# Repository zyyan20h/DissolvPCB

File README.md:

# DissolvPCB 
### Fully Recyclable Electronics with Liquid Metal Conductors and 3D-Printed PVA Substrates
DissolvPCB is a fully recyclable printed circuit board assembly (PCBA) manufacturing technique 
that utilizes affordable FDM 3D printing with Polyvinyl Alcohol (PVA) as a water-soluble substrate 
and eutectic gallium-indium (EGaIn) as the conductive material. 

This Github repository contains the Python macro component used during the DissolvPCB fabrication process. 
The macro enables users to design custom PCB assemblies using standard practices, then automatically
convert the design into a 3D model ready to be printed. Also included are some PCB design examples that 
were used for the demonstration of the DissolvPCB fabrication process. 
Listed below are the prerequisites and instructions on how to utilize this tool. 
Detailed instructions on the entire DisssolvPCB fabrication process can be found under [DissolvPCB Processs Details](DissolvPCB_Process_Details.md).

Please see the [paper](https://www.arxiv.org/abs/2507.22193) for more details on development, implementation, and evaluation of DissolvPCB, and if you use DissolvPCB in your work, please consider to cite the following paper:
```
@article{yan2025dissolvpcb,
  title={DissolvPCB: Fully Recyclable 3D-Printed Electronics with Liquid Metal Conductors and PVA Substrates},
  author={Yan, Zeyu and Hong, SuHwan and Hester, Josiah and Cheng, Tingyu and Peng, Huaishu},
  publisher = {Association for Computing Machinery},
  url = {https://doi.org/10.1145/3746059.3747604},
  year={2025}，
  booktitle = {Proceedings of the 38th Annual ACM Symposium on User Interface Software and Technology}
}
```

## Installation 

### Prerequisites
  - Python 3.0.0 or above
  - FreeCAD 1.0.0 or above
    - https://www.freecad.org/downloads.php
  - KiCAD 8.0.7 or above
    - https://www.kicad.org/download/

### KiCAD Libraries Installation
  - Add Symbol Library
    - Located in /libray/PVA_board.kicad_sym
    - Add by going to: Symbol Editor -> File -> Add Library
  - Add Footprint Library
    - Located in /library/PVA_board.pretty
    - Add by going to: Footprint Editor -> File -> Add Library
  - Copy 3D moddels to KiCAD 3D Models
    - Copy the folder /library/PVA_Board_3Dmodels into directory
    - Set Global Variable "KICAD_3DMODEL_DIR" to correct directory
      - Usually Located under C:\Program Files\KiCad\8.0\share\kicad\3dmodels
      - You can locate the direcotry by going to the KiCAD project window, then Preferences -> Configure Paths
   
## DissolvPCB Design in KiCAD
### PCB Schematic Design
  If you have imported the libraries as described above, the schematic design follows standard procedues.
  During the footprint assignment at the end of your schematic design procecss, verify that 
  footprints are from the PVA_Board library.
    
### PCB Layout Design
  To ensure compatibility with the DissolvPCB fabrication process, a few settings must be changed first. 
  The DRC settings can simply be imported from /KiCAD/DRC_Import_Prj/DRC_Import/DRC_Import.kicad_pcb, using the "Import Settings from Another Board" button under File -> Board Setup. 
  By importing "Design rule constraints", "Predefined track & via dimensions", and "Violation severities" (optional), 
  the PCB design will become compatible with the DissolvPCB fabrication process. (See attached below)

## Macro Execution
FreeCAD has built-in support for Python macros. 
To run, open the Python script by going to File -> Open and open /Python/create.py.
Then, run the macro by going to Macro -> Run Macro. 
Note that the boolean process step at the end can take some time depending on the complexity of your design and your compute power. 
Therefore, it is recommended that you run the macro on a system with a more powerful CPU if possible.

### Macro Functions
The Python scripts contain code comments throughout to help users debug and modify. Overall, the 4 main steps of the macro includes:
- Trace & Pad Generation
- DissolvPCB Body Creation
- 3D Footprint Insertion
- Boolean Operation

Except for the Boolean Operation, these parts are independant of each other. 
Thus, it is possible to run any combination of of the first 3 as desired. 

*Note: If the boolean operation fails from an error relating to 'multiple bodies', you may have to enable a setting. 
Go to Edit -> Preferences -> Part/Part Design -> Experimental -> check "Allow multiple solids in Part Design Body by Defualt"

## Examples 

Some KiCAD Designs are provided, which are listed below.
Note that Circuit_sample_01, circuit_sample_02, and ESP_Speaker designs are directly compatible with the macro, and does not require any modifications to replicate our designs. 
  - /KiCAD/circuit_sample/circuit_sample_01
    - Hall Sensor & ATTiny85 design, used throughout the paper
      
  - /KiCAD/circuit_sample/circuit_sample_02
    - Identical Hall Sensor & ATTiny85 design, but with different board outline
	- /KiCAD/circuit_sample/recycled_driver
		- Motor driver circuit design, used to demonstrate the capabilities of the recycled PVA filament
  - /KiCAD/ESP_Breakout
    - Breakout board(s) designed to house the ESP32 board used for the ESP_Speaker Design
    - The version utilized on the paper is the "2mm_2row_esp_breakout" design
  - /KiCAD/ESP_Speaker
    - ESP32-based bluetooth speaker design.
    - The exact design used on the paper demo is "rev_2_ESP_Speaker_2row_esp"
    - Alternatively, a design with components only on one side is under "rev_3_ESP_Speaker_2row_esp"
      
  - /KiCAD/fidget
    - Fidget toy example used on the paper, utilizing a 3D circuit design process.

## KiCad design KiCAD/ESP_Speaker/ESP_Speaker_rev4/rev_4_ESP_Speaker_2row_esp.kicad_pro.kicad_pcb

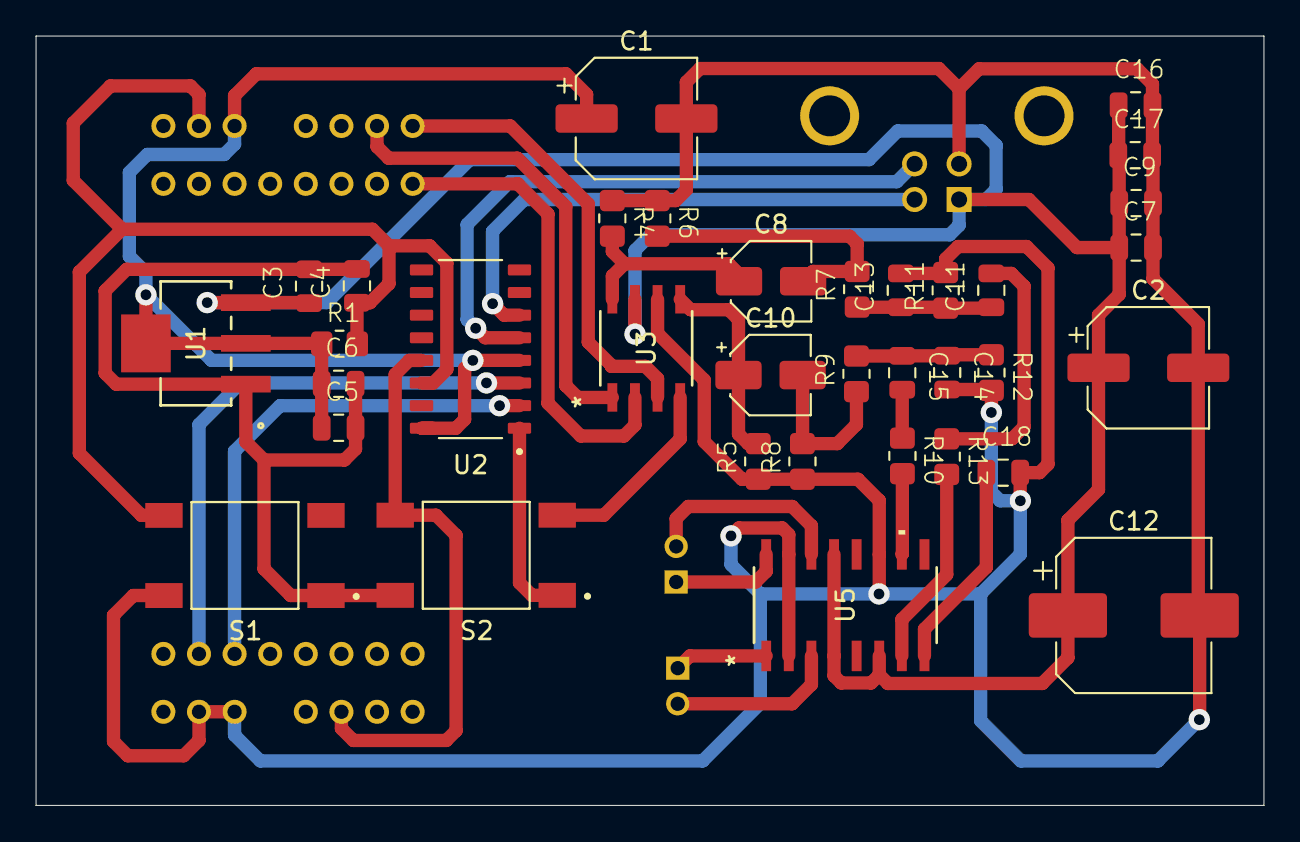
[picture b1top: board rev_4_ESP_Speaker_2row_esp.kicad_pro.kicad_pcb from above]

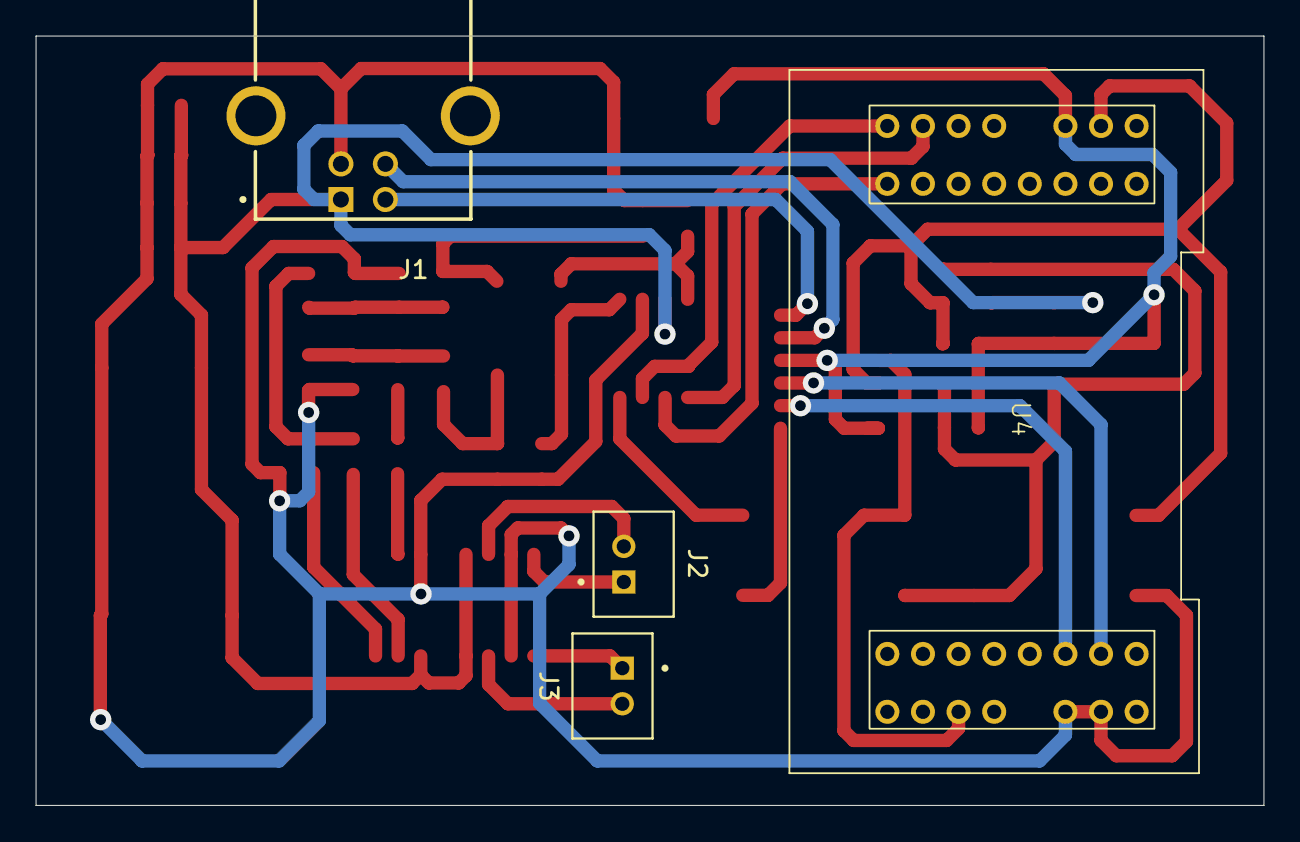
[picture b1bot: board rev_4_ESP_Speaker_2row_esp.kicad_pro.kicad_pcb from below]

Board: 2 copper layers, 69.0 x 43.2 mm, 39 parts (4 on the bottom side), 28 nets.

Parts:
C1, C2: 22uF; CP_Elec_6.3x5.4
C3, C5: 100nF; C-0805
C4, C7, C16, C17: 1uF; C-0805
C6, C9: 0.1uF; C-0805
C8, C10: 3.3uF; CP_Elec_4x5.4
C11, C15: 0.47uF; C-0805
C12: 470uF; CP_Elec_8x10.5
C13, C14: 6nF; C-0805
C18: .1uF; C-0805
J1: USB-B; SAMTEC_USB-B-S-X-X-TH
J2: Audio_R; JST_B2B-PH
J3: Audio_L; JST_B2B-PH
R1, R6, R8: 10k; R-0805
R4, R5: 267k; R-0805
R7, R9: 560; R-0805
R10, R13: 20k; R-0805
R11, R12: 22k; R-0805
S1, S2: 1571527-2; SW_4pin_SMD
U1: AMS1117; SOT_AMS_ADS-M
U2: CH340C; CH430C_SOP16
U3: CS4334-KSZ; CIR-SOIC-8_W150-M
U4: 2mm_2row_esp32_breakout
U5: PAM8403DR; SOIC_8403DR_PAM8403-M

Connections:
+3.3V: C1.1, C5.1, C6.1, R1.1, U1.2 (VOUT), U1.4 (EPAD), U2.4 (V3), U2.16 (VCC), U4.1 (3V3)
+5V: C2.1, C3.1, C7.1, C9.1, C12.1, C16.1, C17.1, J1.1 (VCC), U1.3 (VIN), U3.7 (VA), U5.4 (PVDD), U5.6 (VDD), U5.13 (PVDD)
/Audio-Amp/Audio_R: C14.1, C15.1, R9.2, R12.1
/Audio-Amp/Audo_L: C11.1, C13.1, R7.1, R11.1
/Audio-Amp/L+: J3.1, U5.1 (+OUT_L)
/Audio-Amp/L-: J3.2, U5.3 (-OUT_L)
/Audio-Amp/R+: J2.1, U5.16 (+OUT_R)
/Audio-Amp/R-: J2.2, U5.14 (-OUT_R)
/BCLK: U3.2 (DEM/SCLK), U4.11 (IO27)
/Data: U3.1 (SDATA), U4.13 (IO12)
/EN: C4.1, R1.2, S1.3, S1.4, U2.14 (~RTS), U4.2 (EN)
/IO0: S2.3, S2.4, U2.13 (~DTR), U3.4 (MCLK), U4.29 (IO0)
/RX_ESP: U2.2 (TXD), U4.21 (RXD0)
/TX_ESP: U2.3 (RXD), U4.20 (TXD0)
/WS: U3.3 (LRCK), U4.12 (IO14)
D+: J1.3 (D+), U2.5 (UD+)
D-: J1.2 (D-), U2.6 (UD-)
GND: C1.2, C2.2, C3.2, C4.2, C5.2, C6.2, C7.2, C9.2, C12.2, C13.2, C14.2, C16.2, C17.2, C18.2, J1.4 (GND), R4.1, R5.1, R6.1, R8.1, R11.2, R12.2, S1.1, S1.2, S2.1, S2.2, U1.1 (GND/ADJ), U2.1 (GND), U3.6 (AGND), U4.16 (GND), U4.17 (GND), U5.2 (PGND), U5.11 (GND), U5.15 (PGND)
unnamed: C8.2, R6.2, R7.2
unnamed: C10.2, R8.2, R9.1
unnamed: C11.2, R13.1
unnamed: C15.2, R10.1
unnamed: J1.S1 (SHIELD), J1.S2 (SHIELD)
unnamed: C8.1, R4.2, U3.8 (AOUTL)
unnamed: C10.1, R5.2, U3.5 (AOUTR)
unnamed: R13.2, U5.7 (INL)
unnamed: R10.2, U5.10 (INR)
unnamed: C18.1, U5.8 (VREF)

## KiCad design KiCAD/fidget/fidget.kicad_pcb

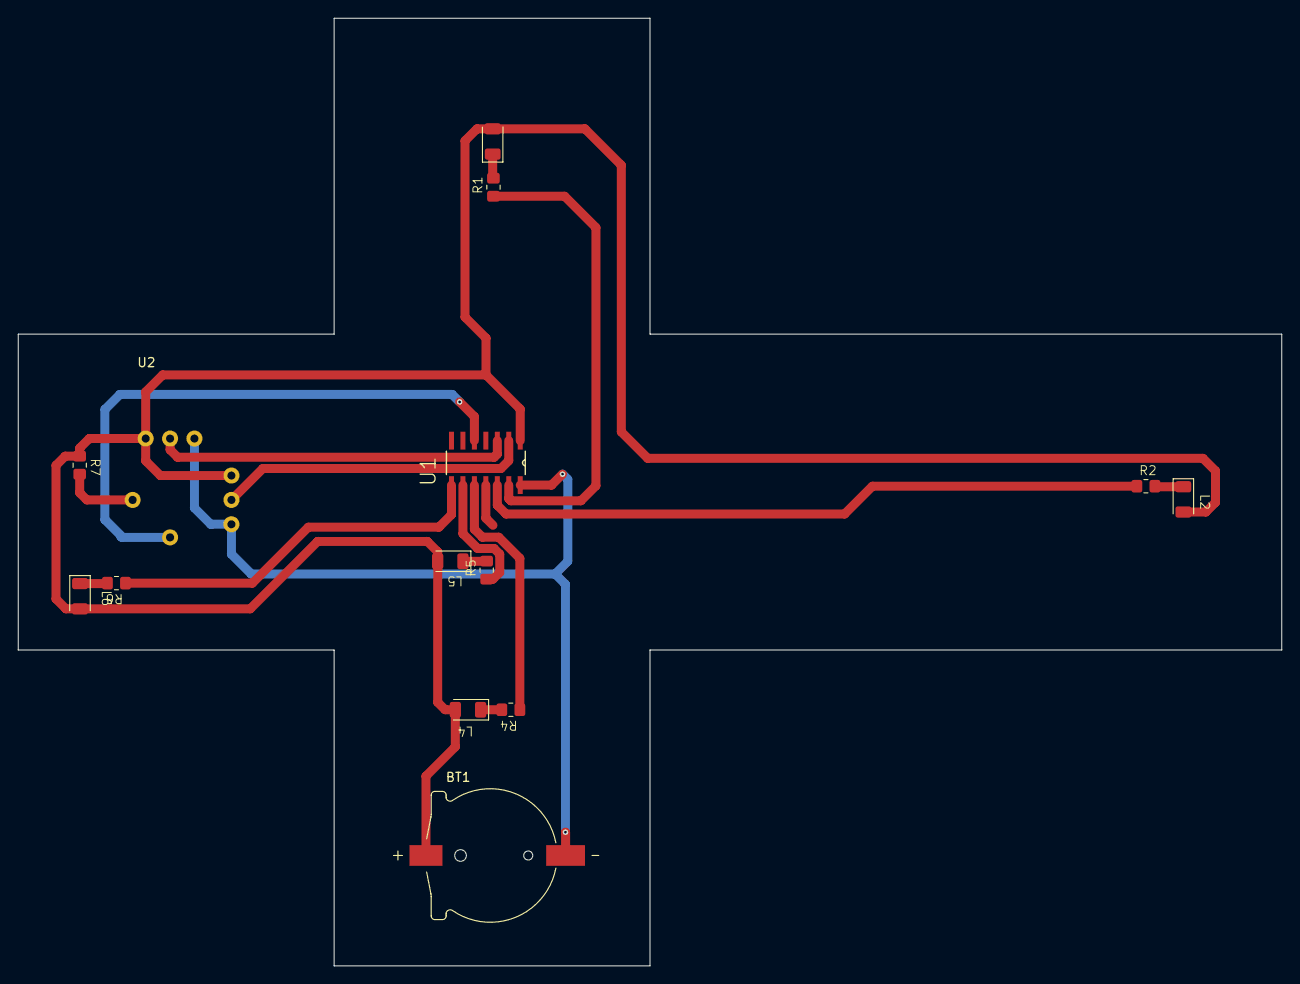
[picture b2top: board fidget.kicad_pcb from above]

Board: 2 copper layers, 140.0 x 105.0 mm, 14 parts (0 on the bottom side), 16 nets.

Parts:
BT1: CH291-1220LF; BAT_CH291-1220LF
L1, L2, L4, L5, L6: LED-1206
R1, R2, R4, R5, R6, R7: R-0805
U1: SOIC-14
U2: COM-09032; Joystick

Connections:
/GND: BT1.N, U1.14, U2.H3 (H-), U2.V3 (V-)
/L1: R1.1, U1.13
/L2: R2.1, U1.12
/L4: R4.1, U1.10
/L5: R5.1, U1.9
/L6: R6.1, U1.8
/S1: U1.3, U2.V2 (V)
/S2: U1.2, U2.H2 (H)
/S3: U1.5, U2.Sb
/VCC: BT1.P, L1.2 (A), L2.2 (A), L4.2 (A), L5.2 (A), L6.2 (A), R7.1, U1.1, U2.H1 (H+), U2.V1 (V+)
unnamed: L1.1 (K), R1.2
unnamed: L2.1 (K), R2.2
unnamed: L4.1 (K), R4.2
unnamed: L5.1 (K), R5.2
unnamed: L6.1 (K), R6.2
unnamed: R7.2, U2.Sa

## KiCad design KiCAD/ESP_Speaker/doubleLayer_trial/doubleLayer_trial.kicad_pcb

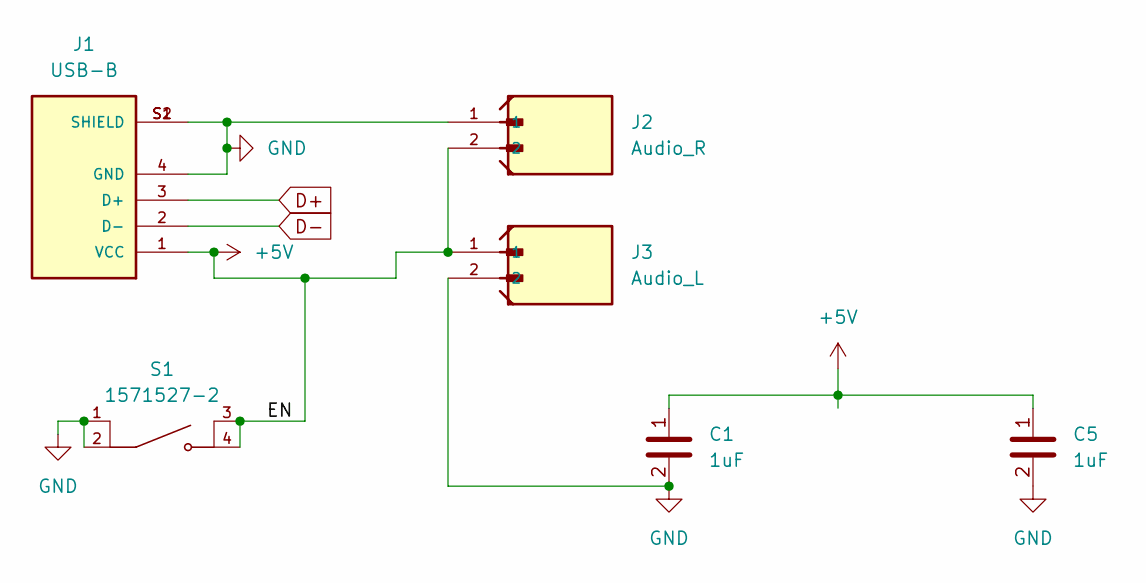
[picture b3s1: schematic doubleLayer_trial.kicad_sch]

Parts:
C1, C5: 1uF; C-0805
J1: USB-B; SAMTEC_USB-B-S-X-X-TH
J2: Audio_R; JST_B2B-PH
J3: Audio_L; JST_B2B-PH
S1: 1571527-2; SW_4pin_SMD

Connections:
+5V: C1.1, C5.1, J1.1 (VCC), J2.2, J3.1, S1.3, S1.4
D+: J1.3 (D+)
D-: J1.2 (D-)
GND: C1.2, C5.2, J1.4 (GND), J1.S1 (SHIELD), J1.S2 (SHIELD), J2.1, J3.2, S1.1, S1.2

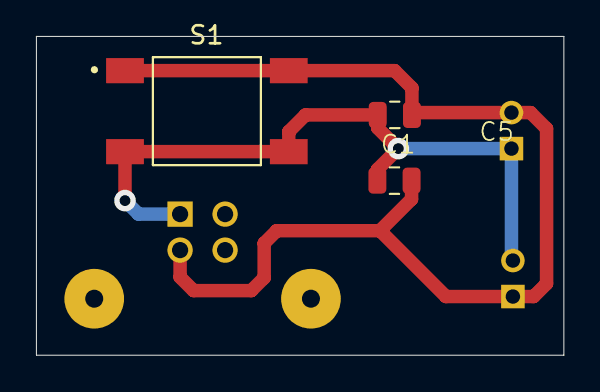
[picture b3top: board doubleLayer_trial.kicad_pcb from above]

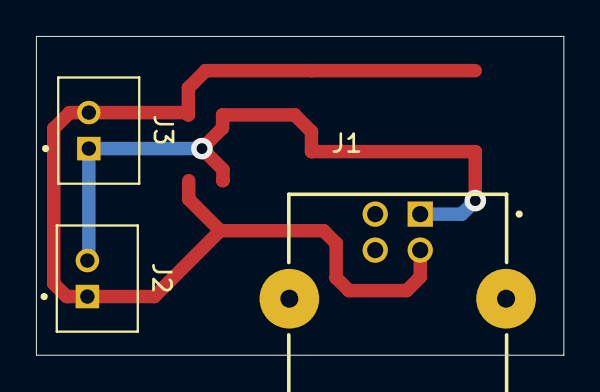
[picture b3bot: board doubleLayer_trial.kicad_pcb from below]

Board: 2 copper layers, 29.3 x 17.7 mm, 6 parts (3 on the bottom side), 2 nets.

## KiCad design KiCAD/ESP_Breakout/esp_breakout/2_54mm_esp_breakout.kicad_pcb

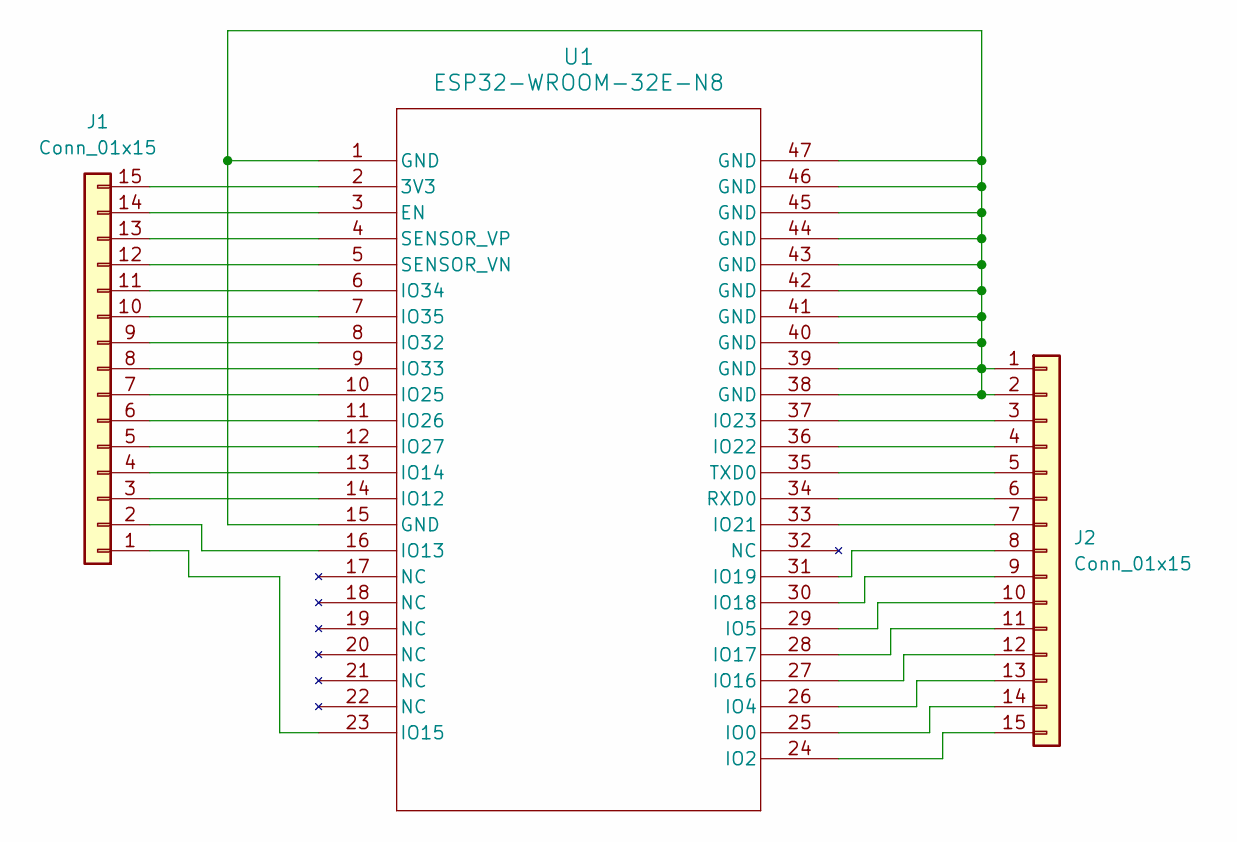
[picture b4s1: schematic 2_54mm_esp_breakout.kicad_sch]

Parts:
J1, J2: Conn_01x15; PinHeader_1x15_P2.54mm_Vertical
U1: ESP32-WROOM-32E-N8; ESP32­WROOM­32E_EXP

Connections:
unnamed: J1.1, U1.23 (IO15)
unnamed: J1.2, U1.16 (IO13)
unnamed: J1.3, U1.14 (IO12)
unnamed: J1.4, U1.13 (IO14)
unnamed: J1.5, U1.12 (IO27)
unnamed: J1.6, U1.11 (IO26)
unnamed: J1.7, U1.10 (IO25)
unnamed: J1.8, U1.9 (IO33)
unnamed: J1.9, U1.8 (IO32)
unnamed: J1.10, U1.7 (IO35)
unnamed: J1.11, U1.6 (IO34)
unnamed: J1.12, U1.5 (SENSOR_VN)
unnamed: J1.13, U1.4 (SENSOR_VP)
unnamed: J1.14, U1.3 (EN)
unnamed: J1.15, U1.2 (3V3)
unnamed: J2.1, J2.2, U1.1 (GND), U1.15 (GND), U1.38 (GND), U1.39 (GND), U1.40 (GND), U1.41 (GND), U1.42 (GND), U1.43 (GND), U1.44 (GND), U1.45 (GND), U1.46 (GND), U1.47 (GND)
unnamed: J2.3, U1.37 (IO23)
unnamed: J2.4, U1.36 (IO22)
unnamed: J2.5, U1.35 (TXD0)
unnamed: J2.6, U1.34 (RXD0)
unnamed: J2.7, U1.33 (IO21)
unnamed: J2.8, U1.31 (IO19)
unnamed: J2.9, U1.30 (IO18)
unnamed: J2.10, U1.29 (IO5)
unnamed: J2.11, U1.28 (IO17)
unnamed: J2.12, U1.27 (IO16)
unnamed: J2.13, U1.26 (IO4)
unnamed: J2.14, U1.25 (IO0)
unnamed: J2.15, U1.24 (IO2)

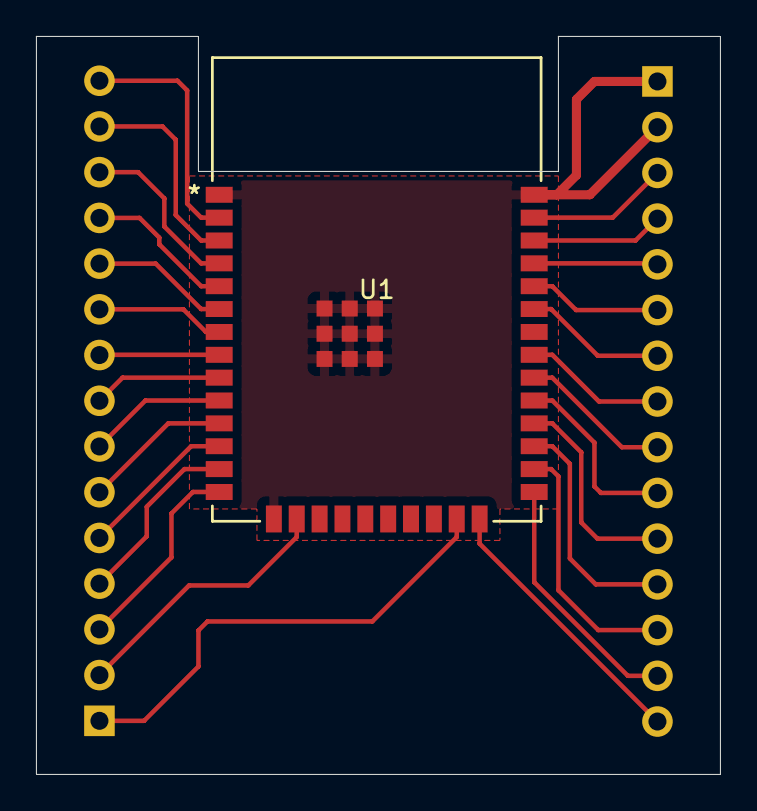
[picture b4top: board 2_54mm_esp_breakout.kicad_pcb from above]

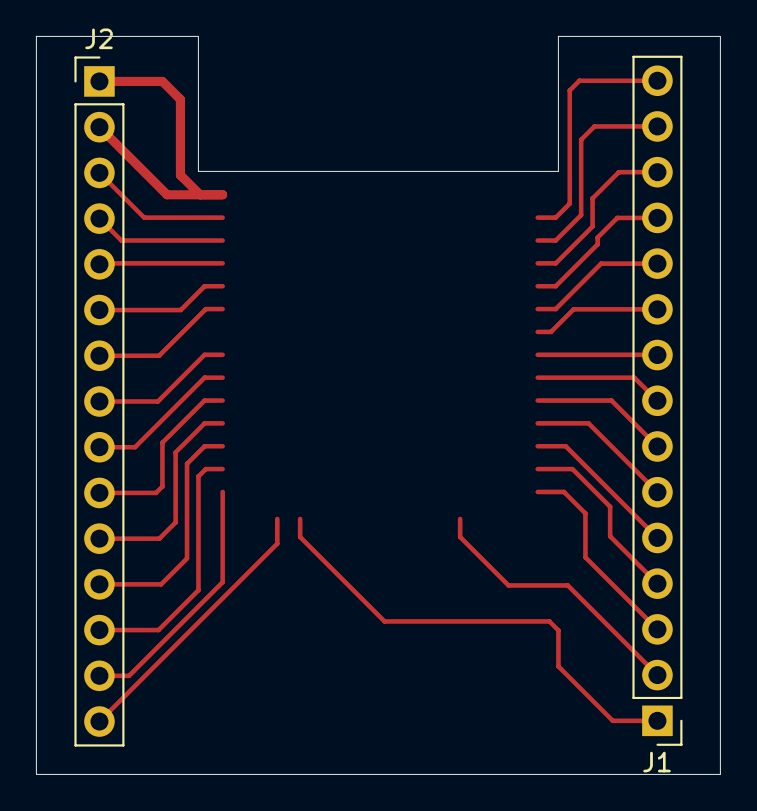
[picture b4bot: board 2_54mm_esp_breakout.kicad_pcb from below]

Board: 2 copper layers, 38.0 x 41.0 mm, 3 parts (2 on the bottom side), 29 nets.

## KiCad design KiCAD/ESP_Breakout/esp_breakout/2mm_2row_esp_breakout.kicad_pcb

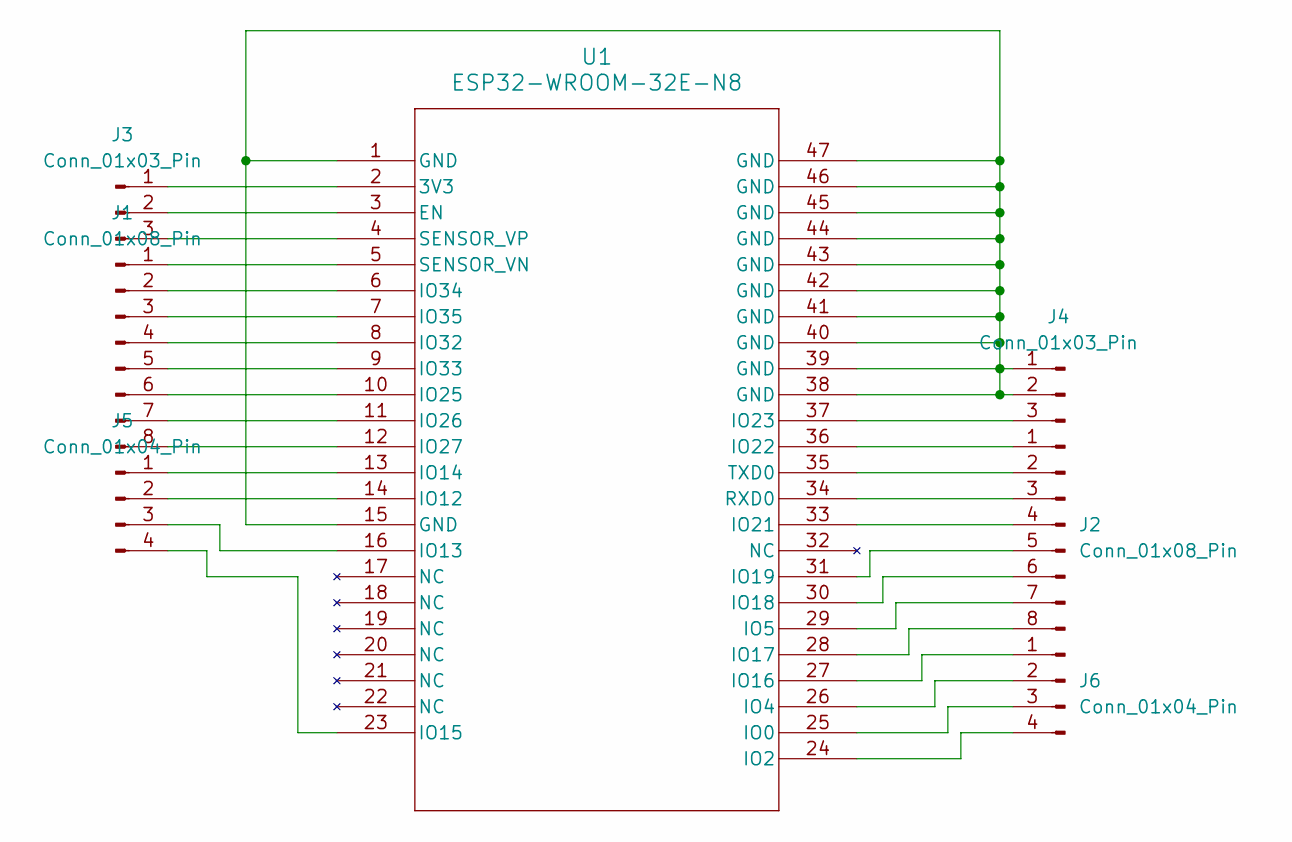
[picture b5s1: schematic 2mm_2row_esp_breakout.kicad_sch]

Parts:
J1, J2: Conn_01x08_Pin
J3, J4: Conn_01x03_Pin
J5, J6: Conn_01x04_Pin
U1: ESP32-WROOM-32E-N8; ESP32­WROOM­32E_EXP

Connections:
unnamed: J1.1, U1.5 (SENSOR_VN)
unnamed: J1.2, U1.6 (IO34)
unnamed: J1.3, U1.7 (IO35)
unnamed: J1.4, U1.8 (IO32)
unnamed: J1.5, U1.9 (IO33)
unnamed: J1.6, U1.10 (IO25)
unnamed: J1.7, U1.11 (IO26)
unnamed: J1.8, U1.12 (IO27)
unnamed: J2.1, U1.36 (IO22)
unnamed: J2.2, U1.35 (TXD0)
unnamed: J2.3, U1.34 (RXD0)
unnamed: J2.4, U1.33 (IO21)
unnamed: J2.5, U1.31 (IO19)
unnamed: J2.6, U1.30 (IO18)
unnamed: J2.7, U1.29 (IO5)
unnamed: J2.8, U1.28 (IO17)
unnamed: J3.1, U1.2 (3V3)
unnamed: J3.2, U1.3 (EN)
unnamed: J3.3, U1.4 (SENSOR_VP)
unnamed: J4.1, J4.2, U1.1 (GND), U1.15 (GND), U1.38 (GND), U1.39 (GND), U1.40 (GND), U1.41 (GND), U1.42 (GND), U1.43 (GND), U1.44 (GND), U1.45 (GND), U1.46 (GND), U1.47 (GND)
unnamed: J4.3, U1.37 (IO23)
unnamed: J5.1, U1.13 (IO14)
unnamed: J5.2, U1.14 (IO12)
unnamed: J5.3, U1.16 (IO13)
unnamed: J5.4, U1.23 (IO15)
unnamed: J6.1, U1.27 (IO16)
unnamed: J6.2, U1.26 (IO4)
unnamed: J6.3, U1.25 (IO0)
unnamed: J6.4, U1.24 (IO2)

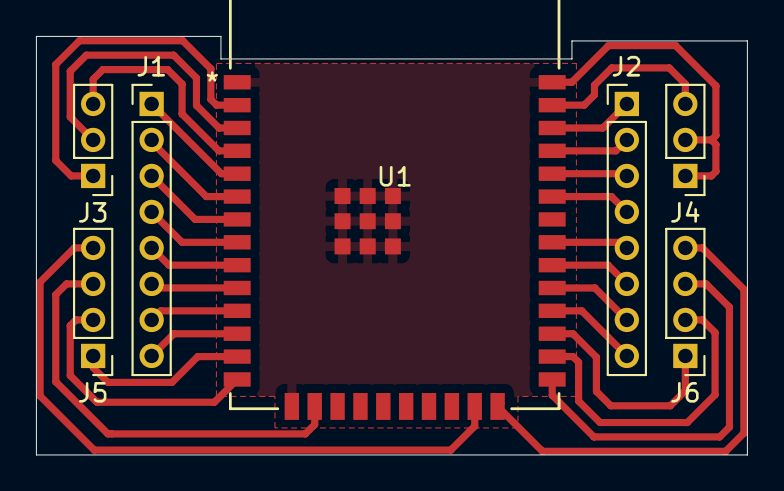
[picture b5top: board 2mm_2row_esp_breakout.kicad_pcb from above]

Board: 2 copper layers, 39.5 x 23.2 mm, 7 parts (0 on the bottom side), 29 nets.

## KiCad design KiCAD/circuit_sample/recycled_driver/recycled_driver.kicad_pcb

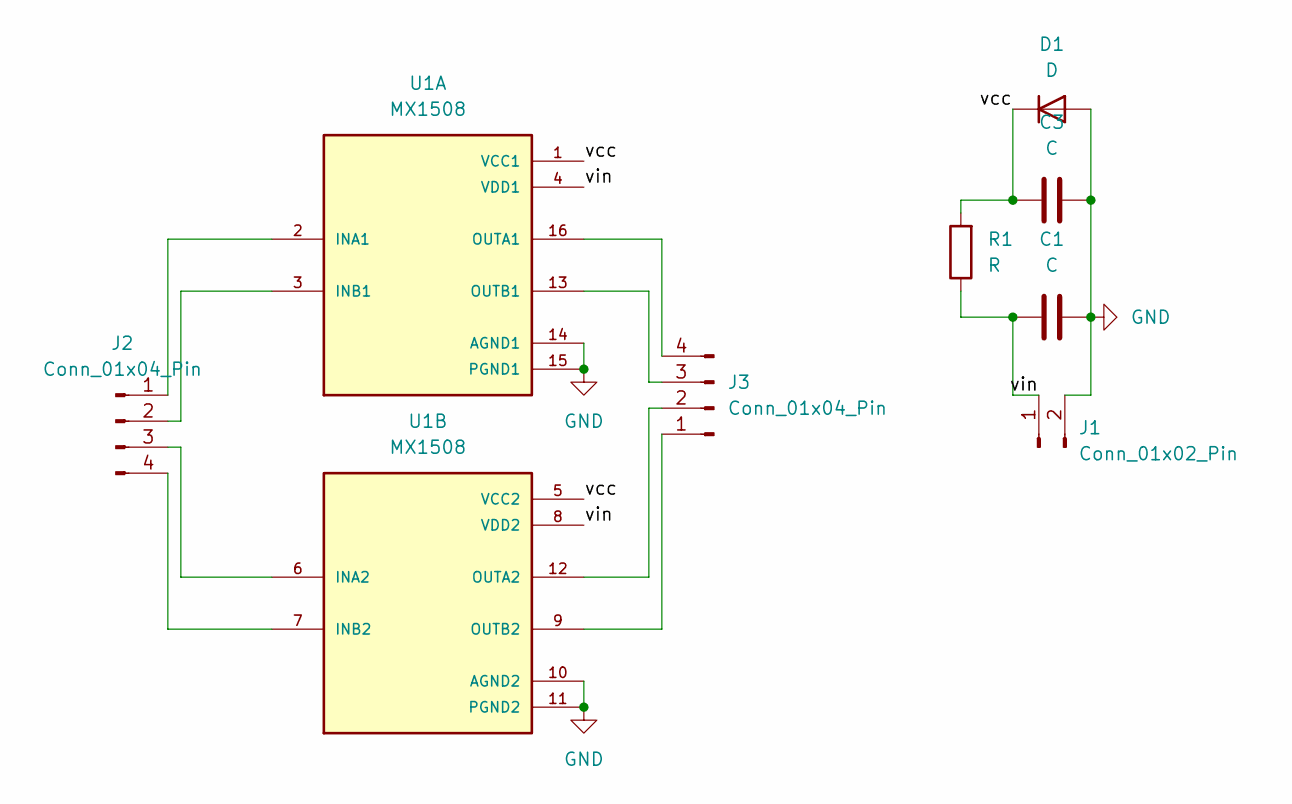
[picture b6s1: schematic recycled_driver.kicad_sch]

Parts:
C1, C3: C; CP_Radial_D5.0mm_P2.00mm
D1: D; D_DO-41_SOD81_P7.62mm_Horizontal
J1: Conn_01x02_Pin; PinHeader_1x02_P2.54mm_Vertical
J2, J3: Conn_01x04_Pin; PinSocket_1x04_P2.54mm_Vertical
R1: R; D_DO-41_SOD81_P7.62mm_Horizontal
U1: MX1508; mx1508

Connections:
/vcc: C3.1, D1.1 (K), R1.2, U1.1 (VCC1), U1.5 (VCC2)
/vin: C1.1, J1.1, R1.1, U1.4 (VDD1), U1.8 (VDD2)
GND: C1.2, C3.2, D1.2 (A), J1.2, U1.10 (AGND2), U1.11 (PGND2), U1.14 (AGND1), U1.15 (PGND1)
unnamed: J2.1, U1.2 (INA1)
unnamed: J2.2, U1.3 (INB1)
unnamed: J2.3, U1.6 (INA2)
unnamed: J2.4, U1.7 (INB2)
unnamed: J3.1, U1.9 (OUTB2)
unnamed: J3.2, U1.12 (OUTA2)
unnamed: J3.3, U1.13 (OUTB1)
unnamed: J3.4, U1.16 (OUTA1)

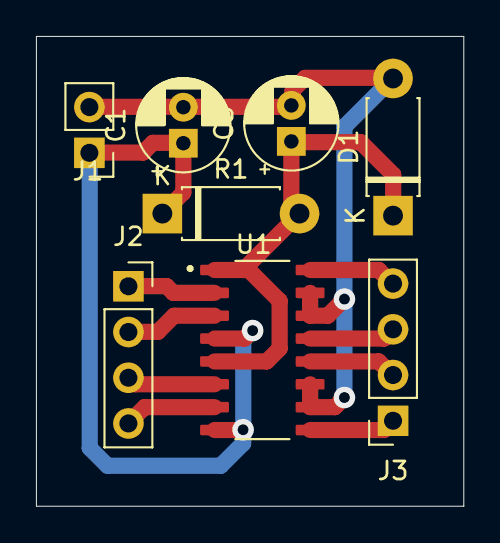
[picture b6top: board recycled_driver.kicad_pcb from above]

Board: 2 copper layers, 23.7 x 26.1 mm, 8 parts (0 on the bottom side), 11 nets.

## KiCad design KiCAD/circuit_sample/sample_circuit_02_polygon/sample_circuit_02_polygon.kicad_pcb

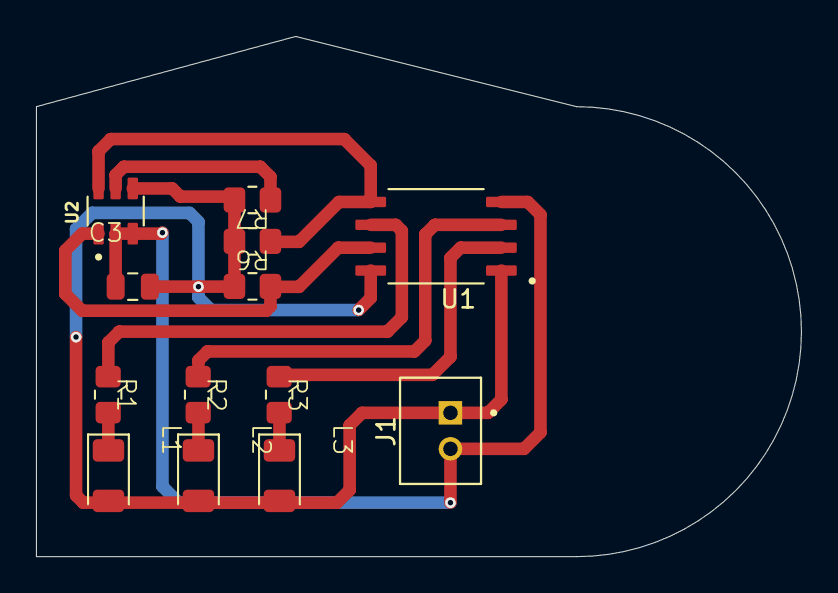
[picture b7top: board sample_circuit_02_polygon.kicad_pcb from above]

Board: 2 copper layers, 42.5 x 28.9 mm, 13 parts (0 on the bottom side), 11 nets.

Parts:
C3: 0.1u; C-0805
J1: B2B-PH; JST_B2B-PH
L1, L2, L3: LED-1206
R1, R2, R3: R-0805
R5, R6: 4.7K; R-0805
R7: 10K; R-0805
U1: SOIC-8
U2: SOT-23-6

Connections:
/INT: R7.1, U2.5
/L1: R1.1, U1.6
/L2: R2.1, U1.3
/L3: R3.1, U1.2
/PB0(MOSI): R6.1, U1.5, U2.6
/PB2(SCK): R5.1, U1.7, U2.1
GND: C3.1, J1.2, U1.4, U2.2, U2.3
unnamed: L1.1 (K), R1.2
unnamed: L2.1 (K), R2.2
unnamed: L3.1 (K), R3.2
VCC: C3.2, J1.1, L1.2 (A), L2.2 (A), L3.2 (A), R5.2, R6.2, R7.2, U1.1, U1.8, U2.4

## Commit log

2025-07-14 new branch
